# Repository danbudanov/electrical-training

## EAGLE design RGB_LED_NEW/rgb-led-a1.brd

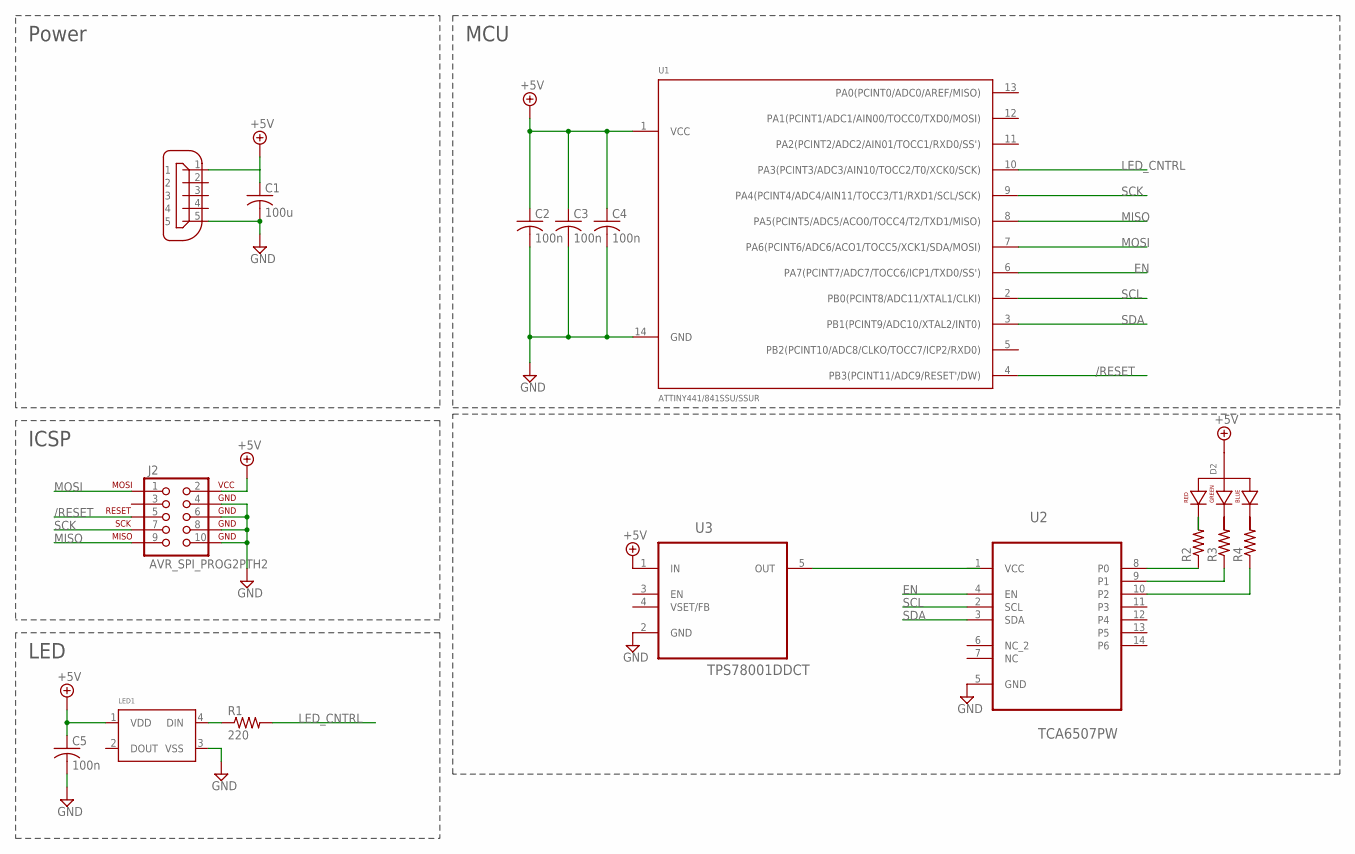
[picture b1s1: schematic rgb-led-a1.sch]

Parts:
C1: 100u; C1206
C2, C3, C4, C5: 100n; C0603
D2: LED-RGB-CA-THRUCLEAR; LED-RGB-THRU
J1: MICRO-USB; GS-14-2180
J2: AVR_SPI_PROG2PTH2; 2X5-SHROUDED
LED1: WS2812B; 5050
R1: 220; R0603
R2, R3, R4: R-US_R0805; R0805
U1: ATTINY441/841SSU/SSUR; SOIC-14
U2: TCA6507PW; SOP65P640X120-14N
U3: TPS78001DDCT; SOT95P280X110-5N

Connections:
+5V: C1.1, C2.1, C3.1, C4.1, C5.1, D2.2 (ANODE), J1.1, J2.2 (VCC), LED1.1 (VDD), U1.1 (VCC), U3.1 (IN)
/RESET: J2.5 (RESET), U1.4 (PB3(PCINT11/ADC9/RESET'/DW))
EN: U1.6 (PA7(PCINT7/ADC7/TOCC6/ICP1/TXD0/SS')), U2.4 (EN)
GND: C1.2, C2.2, C3.2, C4.2, C5.2, J1.5, J2.4 (GND), J2.6 (GND), J2.8 (GND), J2.10 (GND), LED1.3 (VSS), U1.14 (GND), U2.5 (GND), U3.2 (GND)
LED_CNTRL: R1.2, U1.10 (PA3(PCINT3/ADC3/AIN10/TOCC2/T0/XCK0/SCK))
MISO: J2.9 (MISO), U1.8 (PA5(PCINT5/ADC5/ACO0/TOCC4/T2/TXD1/MISO))
MOSI: J2.1 (MOSI), U1.7 (PA6(PCINT6/ADC6/ACO1/TOCC5/XCK1/SDA/MOS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)
unnamed: LED1.4 (DIN), R1.1
unnamed: D2.1 (RED_CATHODE), R2.2
unnamed: R2.1, U2.8 (P0)
unnamed: R3.1, U2.9 (P1)
unnamed: R4.1, U2.10 (P2)
SCK: J2.7 (SCK), U1.9 (PA4(PCINT4/ADC4/AIN11/TOCC3/T1/RXD1/SCL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)
SCL: U1.2 (PB0(PCINT8/ADC11/XTAL1/CLKI)), U2.2 (SCL)
SDA: U1.3 (PB1(PCINT9/ADC10/XTAL2/INT0)), U2.3 (SDA)
VCC: U2.1 (VCC)

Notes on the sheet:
Power
MCU
ICSP
LED

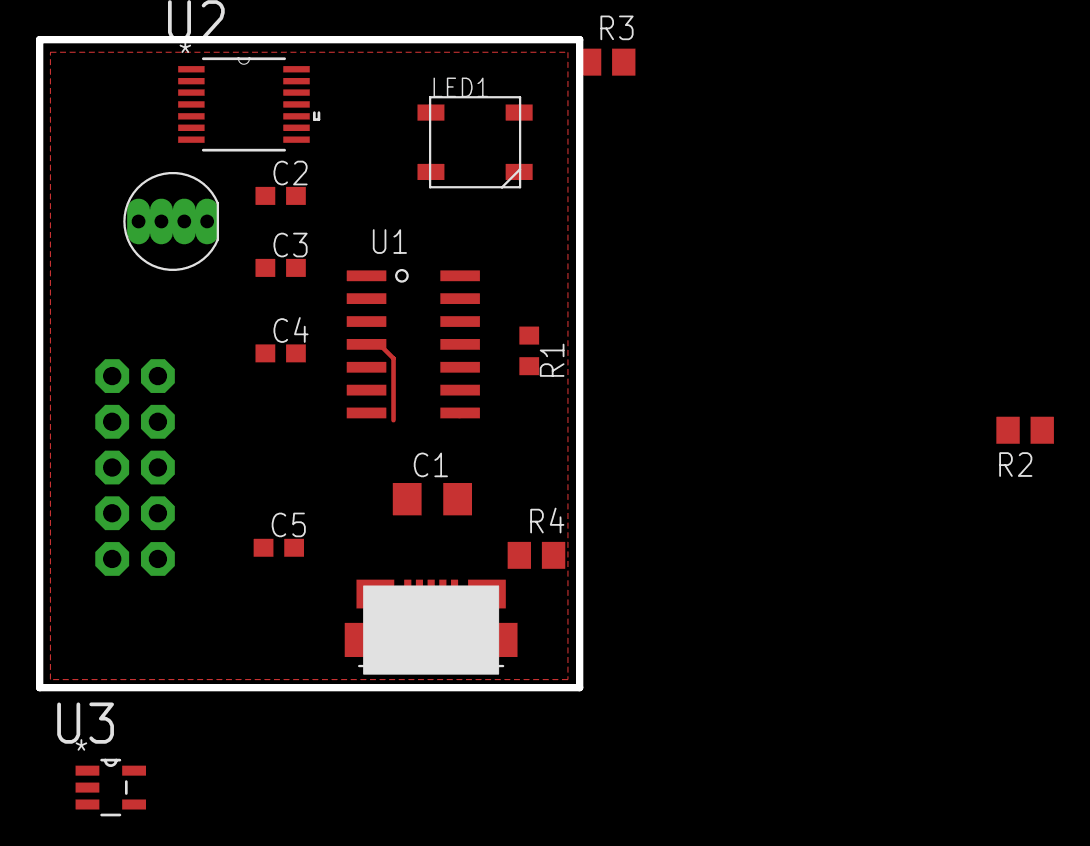
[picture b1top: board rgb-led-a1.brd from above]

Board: 2 copper layers, 30.0 x 36.0 mm, 16 parts (1 on the bottom side), 15 nets.

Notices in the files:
parts and their libraries:
SparkFun-Connectors: Licensing: Creative Commons ShareAlike 4.0 International - https://creativecommons.org/licenses/by-sa/4.0
